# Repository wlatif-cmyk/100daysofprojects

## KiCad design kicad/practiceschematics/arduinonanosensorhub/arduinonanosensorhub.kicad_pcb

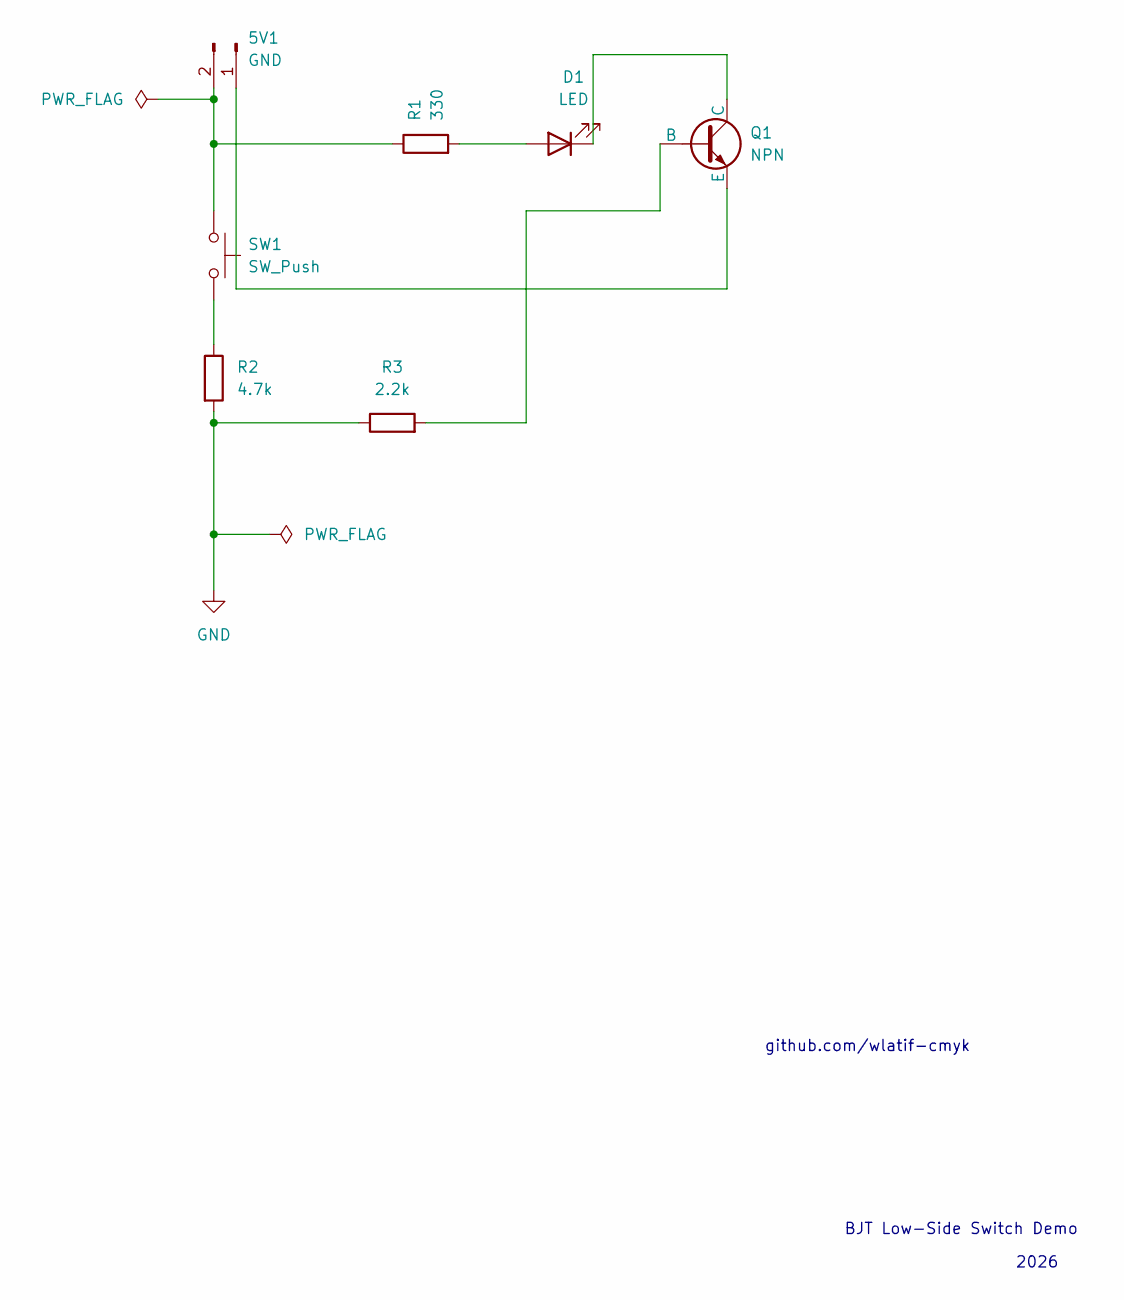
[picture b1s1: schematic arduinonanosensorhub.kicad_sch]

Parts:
5V1: GND; PinHeader_1x02_P2.54mm_Vertical
D1: LED; LED_D3.0mm
Q1: NPN; TO-92_Inline
R1: 330; R_Axial_DIN0207_L6.3mm_D2.5mm_P2.54mm_Vertical
R2: 4.7k; R_Axial_DIN0207_L6.3mm_D2.5mm_P2.54mm_Vertical
R3: 2.2k; R_Axial_DIN0207_L6.3mm_D2.5mm_P2.54mm_Vertical
SW1: SW_Push; SW_PUSH_6mm

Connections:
GND: R2.2, R3.1
unnamed: 5V1.1, Q1.3 (E)
unnamed: 5V1.2, R1.1, SW1.1
unnamed: D1.2 (A), R1.2
unnamed: D1.1 (K), Q1.1 (C)
unnamed: Q1.2 (B), R3.2
unnamed: R2.1, SW1.2

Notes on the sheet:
github.com/wlatif-cmyk
2026
BJT Low-Side Switch Demo

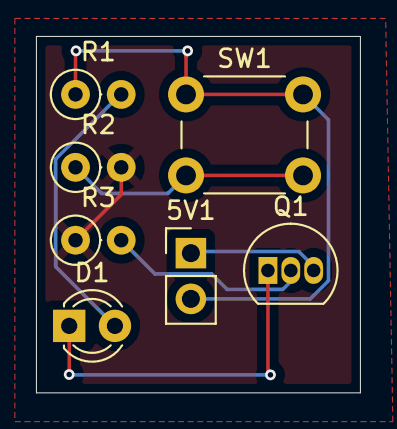
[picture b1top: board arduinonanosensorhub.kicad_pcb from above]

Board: 2 copper layers, 18.0 x 19.8 mm, 7 parts (0 on the bottom side), 7 nets.
